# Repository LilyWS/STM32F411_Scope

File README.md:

Pretty much everything happens in main.c 

Signal conditioning phase consists of a voltage divider, diodes to clamp power to the rails, and an op-amp buffer to ensure proper current to the adc. 

I am interested in adding support for negative voltages through a dc bias to signals. I have yet to test the oscilliscopes capabilities thoroughly although it appears it's unable to accurately determine frequency past 150kHz or so.

The rightmost bread board is just a 555 for testing purposes. The middle one contains the signal condition phase and button inputs (which are still rather bouncy). 
The left most connects the STM32 to the screen, an ILI9488. 
The screen is rather slow to refresh, definetly not the best choice for this project. I regret powering the screen from the F411 as the power rails are rather inconsistent now (hence the need for reading Vrefint to infer true power voltage). I am interested in powering them separately in the future. 

The KiCad project folder for the PCB is the folder name Oscilliscope.

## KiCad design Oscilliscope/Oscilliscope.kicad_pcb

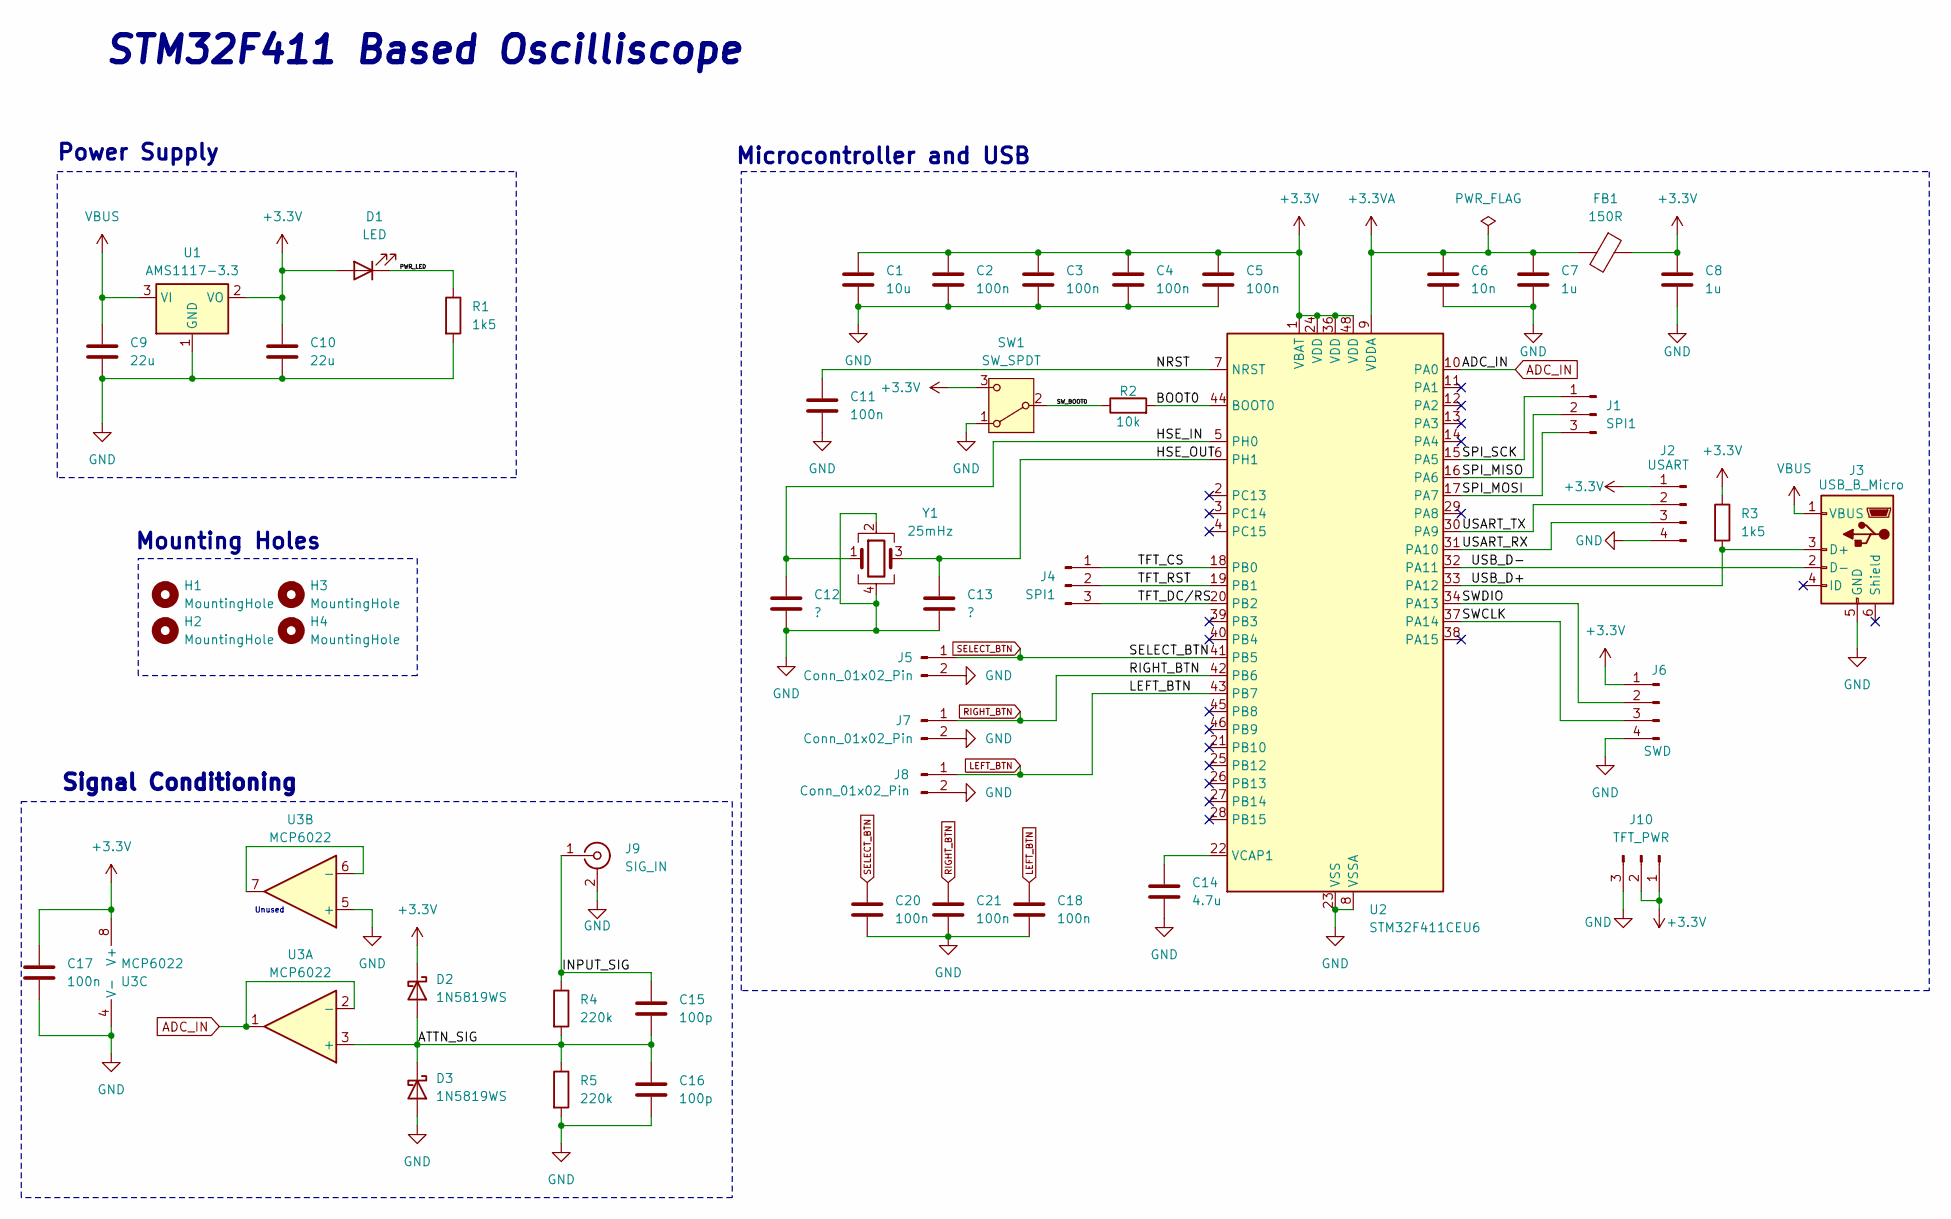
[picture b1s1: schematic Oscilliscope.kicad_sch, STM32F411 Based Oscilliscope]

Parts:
C1: 10u; C_0805_2012Metric
C2, C3, C4, C5, C11, C17, C18, C20, C21: 100n; C_0402_1005Metric
C6: 10n; C_0402_1005Metric
C7, C8: 1u; C_0402_1005Metric
C9, C10: 22u; C_0805_2012Metric
C12, C13: ?; C_0402_1005Metric
C14: 4.7u; C_0805_2012Metric
C15, C16: 100p; C_0402_1005Metric
D1: LED; LED_0603_1608Metric
D2, D3: 1N5819WS; D_SOD-323
FB1: 150R; L_0603_1608Metric
H1, H2, H3, H4: MountingHole; MountingHole_2.2mm_M2
J1, J4: SPI1; PinHeader_1x03_P2.54mm_Vertical
J2: USART; PinHeader_1x04_P2.54mm_Vertical
J3: USB_B_Micro; USB_Micro-B_Wuerth_629105150521
J5, J7, J8: Conn_01x02_Pin; PinHeader_1x02_P2.54mm_Vertical
J6: SWD; PinHeader_1x04_P2.54mm_Vertical
J9: SIG_IN; PinHeader_1x02_P2.54mm_Vertical
J10: TFT_PWR; PinHeader_1x03_P2.54mm_Vertical
R1, R3: 1k5; R_0402_1005Metric
R2: 10k; R_0402_1005Metric
R4, R5: 220k; R_0402_1005Metric
SW1: SW_SPDT; SW_SPDT_PCM12
U1: AMS1117-3.3; SOT-223-3_TabPin2
U2: STM32F411CEU6; QFN-48-1EP_7x7mm_P0.5mm_EP5.6x5.6mm
U3: MCP6022; DIP-8_W7.62mm
Y1: 25mHz; Crystal_SMD_3225-4Pin_3.2x2.5mm

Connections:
+3.3V: C1.1, C2.1, C3.1, C4.1, C5.1, C8.1, C10.1, C17.1, D1.2 (A), D2.1 (K), FB1.1, J2.1, J6.1, J10.1, J10.2, R3.1, SW1.3 (C), U1.2 (VO), U2.1 (VBAT), U2.24 (VDD), U2.36 (VDD), U2.48 (VDD), U3.8 (V+); also elsewhere on the board
+3.3VA: C6.1, C7.1, FB1.2, U2.9 (VDDA)
/ATTN_SIG: C15.2, C16.1, D2.2 (A), D3.1 (K), R4.2, R5.1, U3.3 (+)
/BOOT0: R2.2, U2.44 (BOOT0)
/HSE_IN: C12.1, U2.5 (PH0), Y1.1
/HSE_OUT: C13.1, U2.6 (PH1), Y1.3
/INPUT_SIG: C15.1, J9.1 (In), R4.1
/NRST: C11.1, U2.7 (NRST)
/PWR_LED: D1.1 (K), R1.1
/SPI_MISO: J1.2, U2.16 (PA6)
/SPI_MOSI: J1.3, U2.17 (PA7)
/SPI_SCK: J1.1, U2.15 (PA5)
/SWCLK: J6.3, U2.37 (PA14)
/SWDIO: J6.2, U2.34 (PA13)
/SW_BOOT0: R2.1, SW1.2 (B); also elsewhere on the board
/TFT_CS: J4.1, U2.18 (PB0)
/TFT_DC/RS: J4.3, U2.20 (PB2)
/TFT_RST: J4.2, U2.19 (PB1)
/USART_RX: J2.3, U2.31 (PA10)
/USART_TX: J2.2, U2.30 (PA9)
/USB_D+: J3.3 (D+), R3.2, U2.33 (PA12)
/USB_D-: J3.2 (D-), U2.32 (PA11)
ADC_IN: U2.10 (PA0), U3.1, U3.2 (-)
GND: C1.2, C2.2, C3.2, C4.2, C5.2, C6.2, C7.2, C8.2, C9.2, C10.2, C11.2, C12.2, C13.2, C14.2, C16.2, C17.2, C18.1, C20.1, C21.1, D3.2 (A), J2.4, J3.5 (GND), J5.2, J6.4, J7.2, J8.2, J9.2 (Ext), J10.3, R1.2, R5.2, SW1.1 (A), U1.1 (GND), U2.8 (VSSA), U2.23 (VSS), U2.35 (VSS), U2.47 (VSS), U2.49 (VSS), U3.4 (V-), U3.5 (+), Y1.2, Y1.4; also elsewhere on the board
LEFT_BTN: C18.2, J8.1, U2.43 (PB7)
unnamed: C14.1, U2.22 (VCAP1)
unnamed: U3.6 (-), U3.7
RIGHT_BTN: C21.2, J7.1, U2.42 (PB6)
SELECT_BTN: C20.2, J5.1, U2.41 (PB5)
VBUS: C9.1, J3.1 (VBUS), U1.3 (VI)

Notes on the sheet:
Mounting Holes
Microcontroller and USB
Power Supply
STM32F411 Based Oscilliscope
Unused
Signal Conditioning

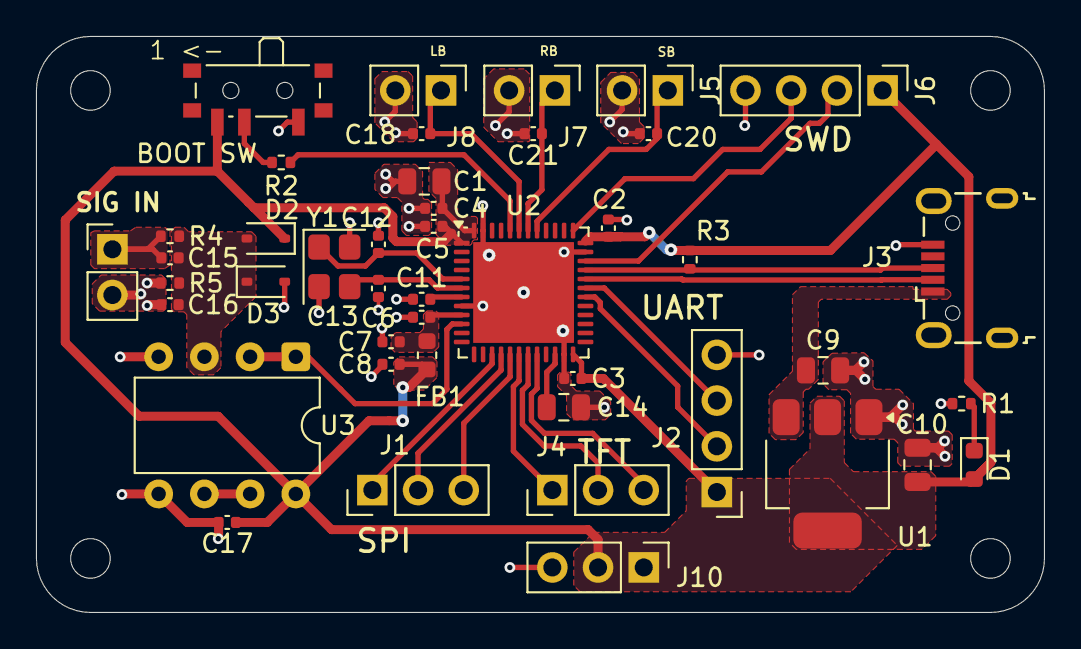
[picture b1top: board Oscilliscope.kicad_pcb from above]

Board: 2 copper layers, 56.0 x 32.0 mm, 48 parts (0 on the bottom side), 30 nets.

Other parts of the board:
BOOT SW: SW_SPDT; SW_SPDT_PCM12

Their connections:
+3.3V: BOOT SW.3 (C); also elsewhere on the board
/SW_BOOT0: BOOT SW.2 (B); also elsewhere on the board
GND: BOOT SW.1 (A); also elsewhere on the board

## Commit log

2025-07-02 first commit
    Uploading project (1)
2025-07-03 Adding Project Files
2025-07-03 Adding Drivers
2025-07-03 Adding Fonts 1
2025-07-03 Adding fonts 2
2025-09-30 Added PCB Files
2025-09-30 PCB Update
